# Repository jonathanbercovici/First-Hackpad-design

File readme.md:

I was inspired to mkae this project so that when you are playing a flight simulator you have acces to all of the most important buttons without ahving to reac acros your whole keyborad, It can aslo be used for FPS games as I designed it to incorperate a space for a wasd and a shift key. THis preject also allowed me to loearn the bacisc of pcb design and the basics of fusion 360.

So that the leds can be seen i am making the case above it very thin this is to help difuse the lights and the make it more strong comapred to holes being cut out.

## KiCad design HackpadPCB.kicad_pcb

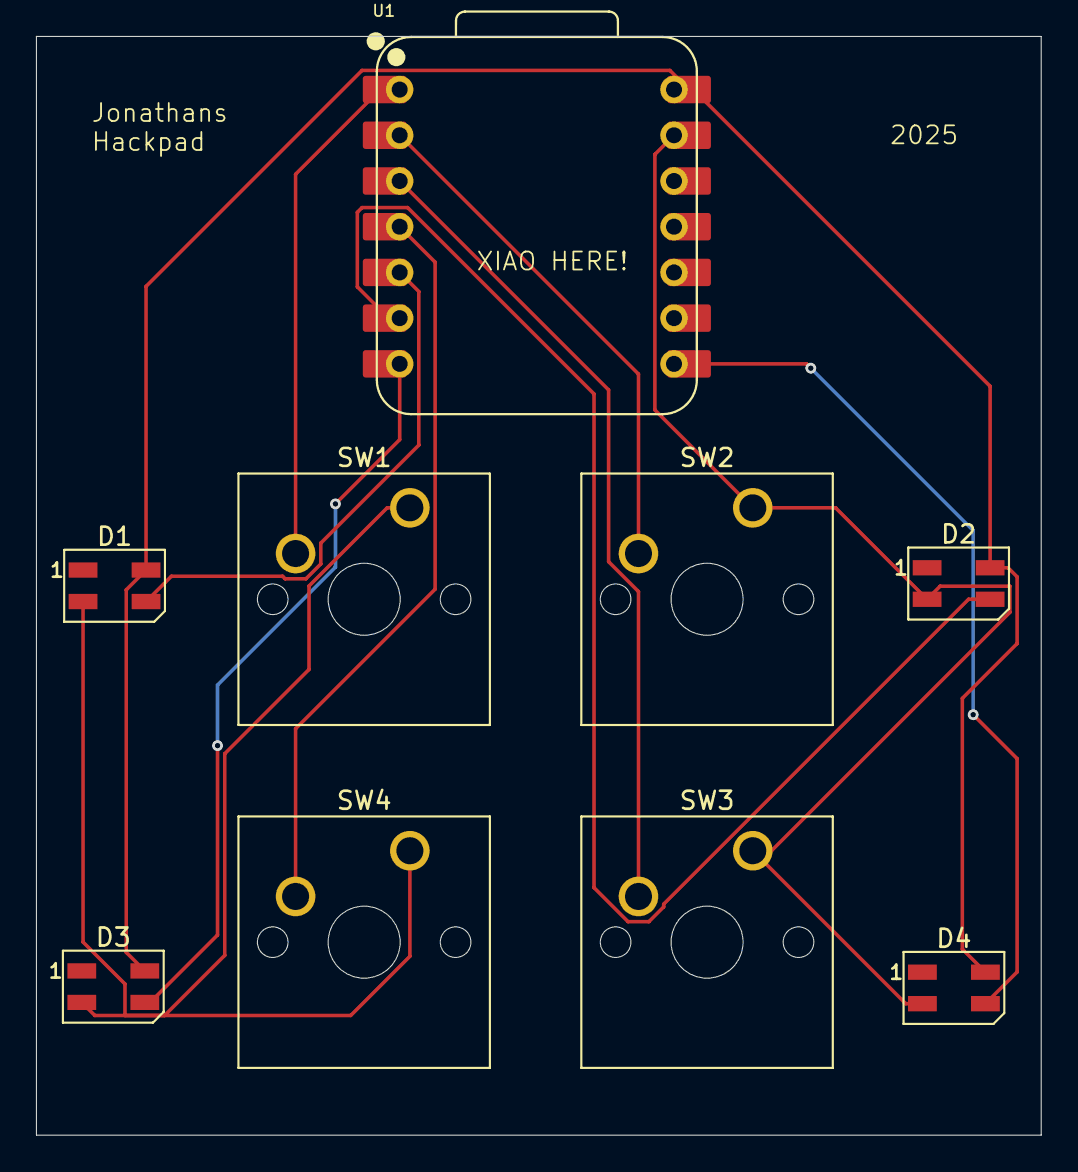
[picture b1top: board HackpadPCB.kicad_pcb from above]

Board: 2 copper layers, 55.8 x 61.0 mm, 9 parts (0 on the bottom side), 10 nets.

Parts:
D1, D2, D3, D4: SK6812MINI; LED_SK6812MINI_PLCC4_3.5x3.5mm_P1.75mm
SW1, SW2, SW3, SW4: SW_Push; SW_Cherry_MX_1.00u_PCB
U1: XIAO-RP2040-DIP

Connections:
unnamed: D1.3 (DIN), U1.5 (GPIO6/SDA)
unnamed: D1.4 (VDD), D2.4 (VDD), D3.4 (VDD), D4.4 (VDD), U1.14 (VBUS)
unnamed: D1.2 (VSS), D2.2 (VSS), D3.2 (VSS), D4.2 (VSS), SW1.1, SW2.1, SW3.1, SW4.1, U1.13 (GND)
unnamed: D2.3 (DIN), U1.6 (GPIO7/SCL)
unnamed: D3.3 (DIN), U1.7 (GPIO0/TX)
unnamed: D4.3 (DIN), U1.8 (GPIO1/RX)
unnamed: SW1.2, U1.1 (GPIO26/ADC0/A0)
unnamed: SW2.2, U1.2 (GPIO27/ADC1/A1)
unnamed: SW3.2, U1.3 (GPIO28/ADC2/A2)
unnamed: SW4.2, U1.4 (GPIO29/ADC3/A3)
